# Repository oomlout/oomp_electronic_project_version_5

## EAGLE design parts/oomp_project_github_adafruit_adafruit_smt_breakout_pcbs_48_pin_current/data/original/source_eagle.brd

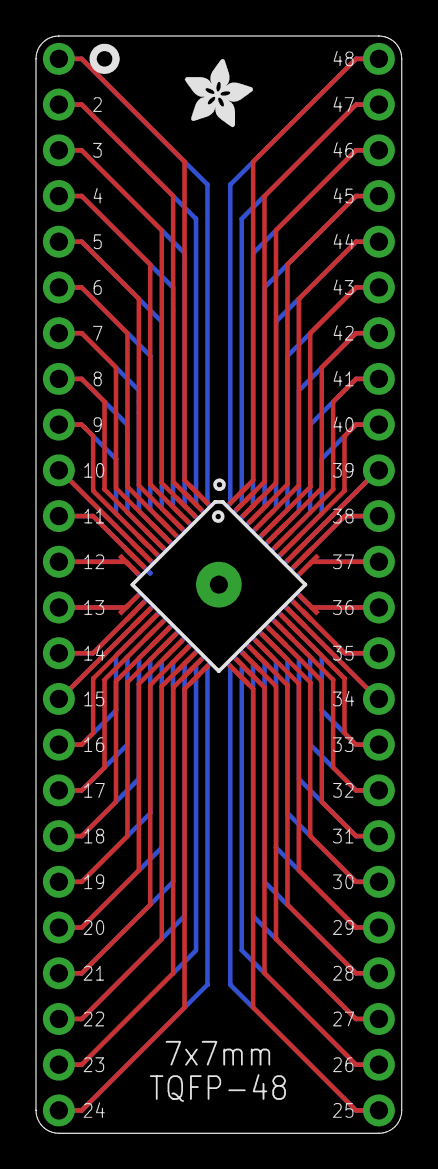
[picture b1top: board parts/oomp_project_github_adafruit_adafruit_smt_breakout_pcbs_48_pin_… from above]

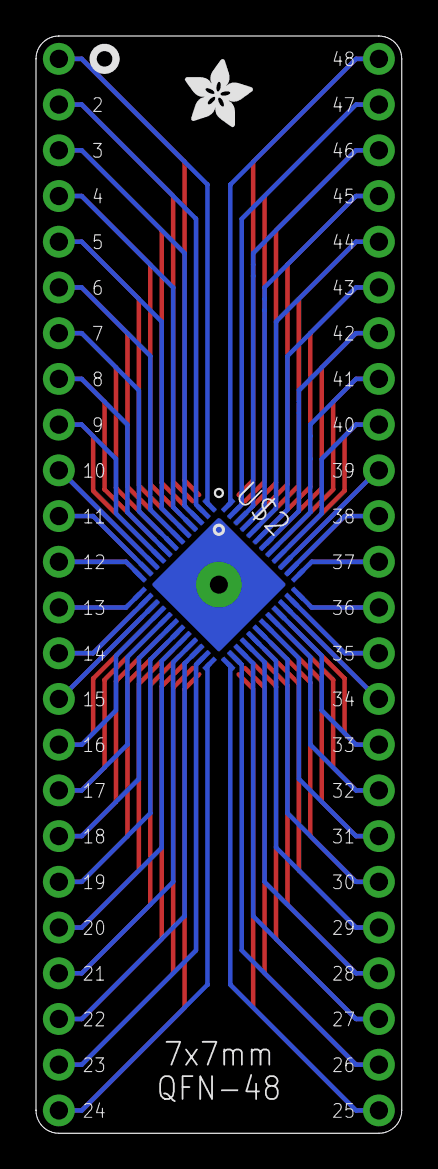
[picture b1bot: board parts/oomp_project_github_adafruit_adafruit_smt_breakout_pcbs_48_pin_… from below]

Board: 2 copper layers, 20.3 x 61.0 mm, 8 parts (2 on the bottom side), 48 nets.

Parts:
JP1, JP2: PADS-14
JP3, JP4: PADS-10
U$1: BREAKOUTS_48-PINTQFP; BREAKOUTS_TQFP48
U$2: BREAKOUTS_48-PINQFN; BREAKOUTS_QFN48
U$3, U$4: ADAFRUIT_3.5MM

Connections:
.05: JP4.6, U$1.29, U$2.20
unnamed: JP1.1, U$1.1, U$2.48
unnamed: JP1.2, U$1.2, U$2.47
unnamed: JP1.3, U$1.3, U$2.46
unnamed: JP1.4, U$1.4, U$2.45
unnamed: JP1.5, U$1.5, U$2.44
unnamed: JP1.6, U$1.6, U$2.43
unnamed: JP1.7, U$1.7, U$2.42
unnamed: JP1.8, U$1.8, U$2.41
unnamed: JP1.9, U$1.9, U$2.40
unnamed: JP1.10, U$1.10, U$2.39
unnamed: JP1.11, U$1.11, U$2.38
unnamed: JP1.12, U$1.12, U$2.37
unnamed: JP3.1, U$1.15, U$2.34
unnamed: JP3.2, U$1.16, U$2.33
unnamed: JP3.3, U$1.17, U$2.32
unnamed: JP3.4, U$1.18, U$2.31
unnamed: JP3.5, U$1.19, U$2.30
unnamed: JP3.6, U$1.20, U$2.29
unnamed: JP3.7, U$1.21, U$2.28
unnamed: JP3.8, U$1.22, U$2.27
unnamed: JP3.9, U$1.23, U$2.26
unnamed: JP3.10, U$1.24, U$2.25
unnamed: JP2.1, U$1.48, U$2.1
unnamed: JP2.2, U$1.47, U$2.2
unnamed: JP2.3, U$1.46, U$2.3
unnamed: JP2.4, U$1.45, U$2.4
unnamed: JP2.5, U$1.44, U$2.5
unnamed: JP2.6, U$1.43, U$2.6
unnamed: JP2.7, U$1.42, U$2.7
unnamed: JP2.8, U$1.41, U$2.8
unnamed: JP2.10, U$1.39, U$2.10
unnamed: JP2.11, U$1.38, U$2.11
unnamed: JP2.12, U$1.37, U$2.12
unnamed: JP4.1, U$1.34, U$2.15
unnamed: JP4.2, U$1.33, U$2.16
unnamed: JP4.3, U$1.32, U$2.17
unnamed: JP4.4, U$1.31, U$2.18
unnamed: JP4.5, U$1.30, U$2.19
unnamed: JP4.7, U$1.28, U$2.21
unnamed: JP4.8, U$1.27, U$2.22
unnamed: JP4.9, U$1.26, U$2.23
unnamed: JP4.10, U$1.25, U$2.24
unnamed: JP1.14, U$1.14, U$2.35
unnamed: JP2.14, U$1.35, U$2.14
unnamed: JP2.13, U$1.36, U$2.13
unnamed: JP1.13, U$1.13, U$2.36
unnamed: JP2.9, U$1.40, U$2.9

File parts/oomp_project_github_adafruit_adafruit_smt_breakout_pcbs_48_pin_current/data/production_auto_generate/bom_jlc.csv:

Comment,Designator,Footprint,LCSC Part #
,"U$3,U$4",48-pin-import-fps:ADAFRUIT_3.5MM,
,"JP3,JP4",48-pin-import-fps:PADS-10,
,"JP1,JP2",48-pin-import-fps:PADS-14,
BREAKOUTS_48-PINQFN,U$2,48-pin-import-fps:BREAKOUTS_QFN48,
BREAKOUTS_48-PINTQFP,U$1,48-pin-import-fps:BREAKOUTS_TQFP48,

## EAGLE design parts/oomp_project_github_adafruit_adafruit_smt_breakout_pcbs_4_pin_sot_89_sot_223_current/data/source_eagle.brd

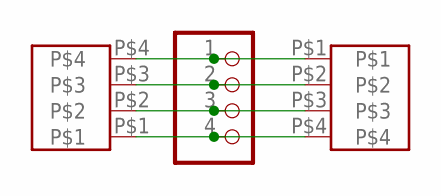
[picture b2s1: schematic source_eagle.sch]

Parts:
JP1: PADS-4
U$1: SOT89
U$2: SOT223

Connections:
unnamed: JP1.1, U$1.P$1, U$2.P$4
unnamed: JP1.2, U$1.P$2, U$2.P$3
unnamed: JP1.3, U$1.P$3, U$2.P$2
unnamed: JP1.4, U$1.P$4, U$2.P$1

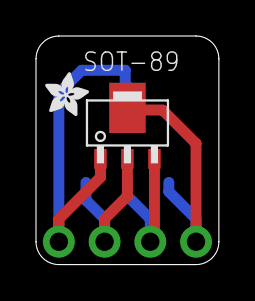
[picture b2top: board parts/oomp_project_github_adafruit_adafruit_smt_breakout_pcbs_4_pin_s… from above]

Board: 2 copper layers, 10.2 x 12.7 mm, 4 parts (1 on the bottom side), 4 nets.

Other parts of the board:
U$3: ADAFRUIT_2.5MM

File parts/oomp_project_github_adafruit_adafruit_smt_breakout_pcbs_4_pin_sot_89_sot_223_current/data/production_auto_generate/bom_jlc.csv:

Comment,Designator,Footprint,LCSC Part #
,U$3,4-pin SOT-89+SOT-223-import-fps:ADAFRUIT_2.5MM,
,JP1,4-pin SOT-89+SOT-223-import-fps:PADS-4,
SOT223,U$2,4-pin SOT-89+SOT-223-import-fps:SOT223,
SOT89,U$1,4-pin SOT-89+SOT-223-import-fps:SOT89,

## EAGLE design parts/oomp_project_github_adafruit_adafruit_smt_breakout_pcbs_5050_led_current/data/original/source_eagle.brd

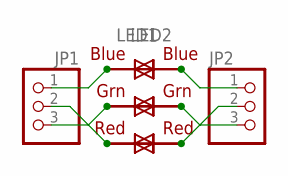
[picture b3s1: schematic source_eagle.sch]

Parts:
JP1, JP2: PINHD-1X3CB; 1X03-CLEANBIG
LED1, LED2: RGBLED5050

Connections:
unnamed: JP1.1, LED1.3 (BLUE_A), LED2.4 (BLUE_C)
unnamed: JP1.2, LED1.2 (RED_A), LED2.5 (RED_C)
unnamed: JP1.3, LED1.1 (GREEN_A), LED2.6 (GREEN_C)
unnamed: JP2.1, LED1.4 (BLUE_C), LED2.3 (BLUE_A)
unnamed: JP2.2, LED1.5 (RED_C), LED2.2 (RED_A)
unnamed: JP2.3, LED1.6 (GREEN_C), LED2.1 (GREEN_A)

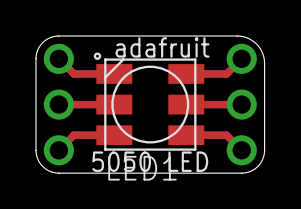
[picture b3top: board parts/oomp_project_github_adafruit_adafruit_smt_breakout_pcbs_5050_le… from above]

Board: 2 copper layers, 12.7 x 7.6 mm, 4 parts (1 on the bottom side), 6 nets.

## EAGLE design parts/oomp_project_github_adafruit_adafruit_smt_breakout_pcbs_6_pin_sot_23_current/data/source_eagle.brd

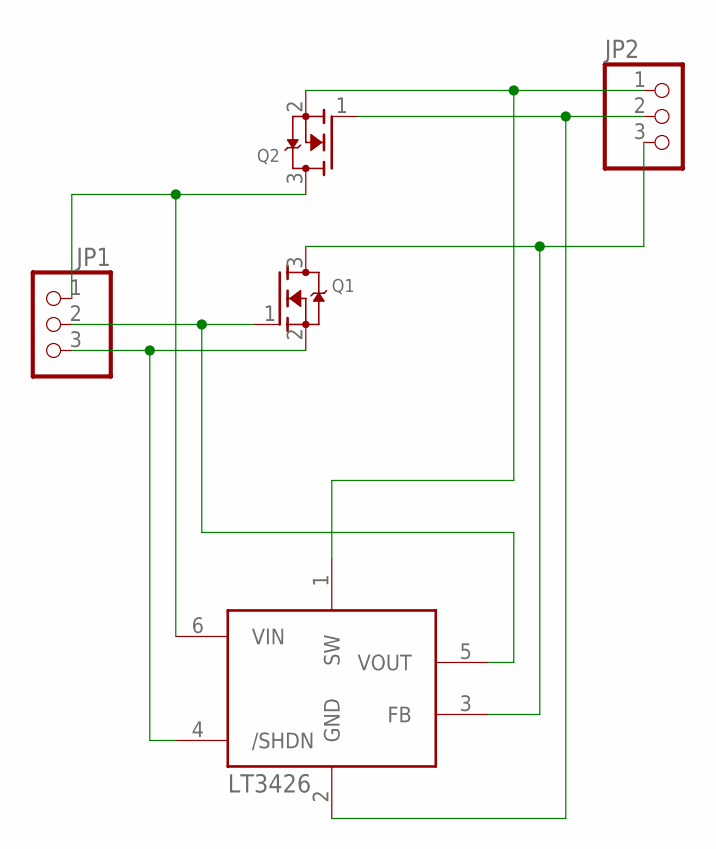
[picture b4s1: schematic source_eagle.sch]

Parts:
JP1, JP2: PINHD-1X3CB; 1X03-CLEANBIG
Q1, Q2: MOSFET-NREFLOW; SOT23
U$1: LT3426; SOT23-6

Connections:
GND: JP2.2, Q2.1 (G), U$1.2 (GND)
unnamed: JP2.3, Q1.3 (D), U$1.3 (FB)
unnamed: JP1.2, Q1.1 (G), U$1.5 (VOUT)
unnamed: JP1.3, Q1.2 (S), U$1.4 (/SHDN)
unnamed: JP2.1, Q2.2 (S), U$1.1 (SW)
unnamed: JP1.1, Q2.3 (D), U$1.6 (VIN)

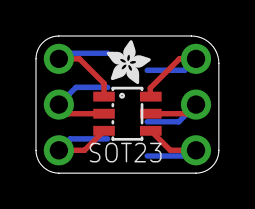
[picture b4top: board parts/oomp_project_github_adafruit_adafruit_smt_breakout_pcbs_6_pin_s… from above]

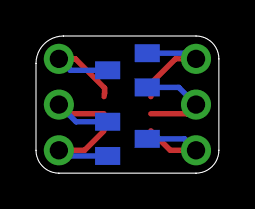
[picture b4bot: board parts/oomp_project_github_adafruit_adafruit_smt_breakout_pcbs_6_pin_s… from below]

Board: 2 copper layers, 10.2 x 7.6 mm, 6 parts (2 on the bottom side), 6 nets.

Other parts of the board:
U$2: ADAFRUIT_2.5MM

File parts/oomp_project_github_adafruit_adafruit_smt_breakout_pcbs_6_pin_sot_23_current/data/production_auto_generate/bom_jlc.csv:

Comment,Designator,Footprint,LCSC Part #
,"JP1,JP2",6-pin SOT-23-import-fps:1X03-CLEANBIG,C49257
,U$2,6-pin SOT-23-import-fps:ADAFRUIT_2.5MM,
,"Q1,Q2",6-pin SOT-23-import-fps:SOT23,
LT3426,U$1,6-pin SOT-23-import-fps:SOT23-6,

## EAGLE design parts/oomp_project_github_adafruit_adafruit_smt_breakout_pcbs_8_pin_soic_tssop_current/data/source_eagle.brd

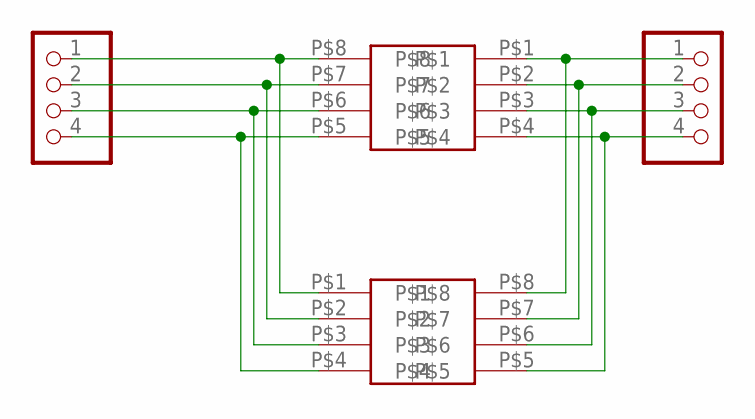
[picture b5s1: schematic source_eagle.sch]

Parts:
CN1, CN2: PADS-4
U$1: 8-PINSOIC-NW; SO8NW
U$2: 8-PINTSSOP; TSSOP8

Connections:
unnamed: CN1.1, U$1.P$8, U$2.P$1
unnamed: CN2.1, U$1.P$1, U$2.P$8
unnamed: CN2.2, U$1.P$2, U$2.P$7
unnamed: CN2.3, U$1.P$3, U$2.P$6
unnamed: CN2.4, U$1.P$4, U$2.P$5
unnamed: CN1.2, U$1.P$7, U$2.P$2
unnamed: CN1.3, U$1.P$6, U$2.P$3
unnamed: CN1.4, U$1.P$5, U$2.P$4

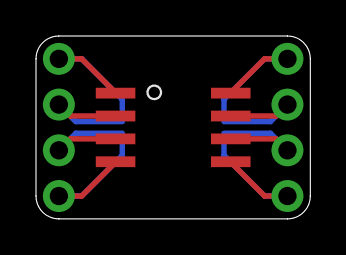
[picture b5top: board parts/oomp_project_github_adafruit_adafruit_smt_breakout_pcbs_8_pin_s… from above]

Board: 2 copper layers, 15.2 x 10.2 mm, 4 parts (1 on the bottom side), 8 nets.

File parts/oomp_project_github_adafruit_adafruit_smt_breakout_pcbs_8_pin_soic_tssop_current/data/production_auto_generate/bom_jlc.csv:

Comment,Designator,Footprint,LCSC Part #
,"CN1,CN2",8-pin SOIC+TSSOP-import-fps:PADS-4,
8-PINSOIC-NW,U$1,8-pin SOIC+TSSOP-import-fps:SO8NW,
8-PINTSSOP,U$2,8-pin SOIC+TSSOP-import-fps:TSSOP8,

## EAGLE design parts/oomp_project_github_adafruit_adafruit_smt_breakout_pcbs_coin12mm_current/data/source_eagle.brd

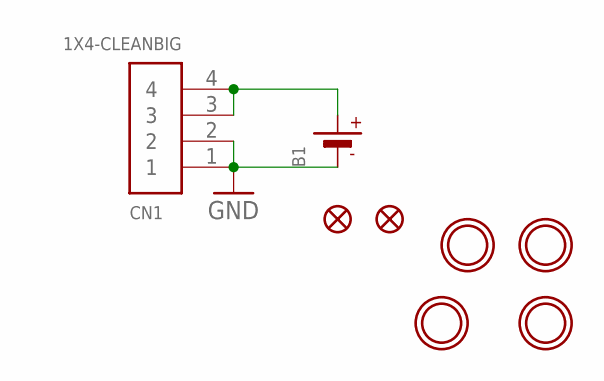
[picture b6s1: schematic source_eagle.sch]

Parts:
B1: BATTERYCR1220_SMT; CR1220
CN1: 1X4-CLEANBIG; 1X04-CLEANBIG
FID1, FID2: FIDUCIAL""; FIDUCIAL_1MM
U$1, U$2, U$3, U$5: MOUNTINGHOLE2.5; MOUNTINGHOLE_2.5_PLATED

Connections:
GND: B1.-, CN1.1, CN1.2
unnamed: B1.+$1 (+), CN1.3, CN1.4

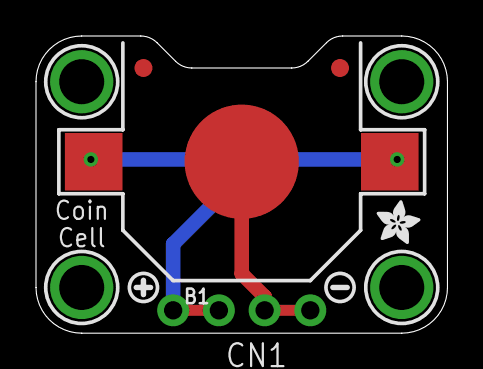
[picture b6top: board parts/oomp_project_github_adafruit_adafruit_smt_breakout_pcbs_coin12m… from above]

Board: 2 copper layers, 22.9 x 16.5 mm, 12 parts (1 on the bottom side), 2 nets.

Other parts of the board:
U$4: ADAFRUIT_5MM
U$6: SYMBOL_PLUS
U$7: SYMBOL_MINUS
U$8: ADAFRUIT_2.5MM

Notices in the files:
parts and their libraries:
microbuilder: This work is placed in the public domain, and may be freely used for commercial and non-commercial work with the following conditions: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
